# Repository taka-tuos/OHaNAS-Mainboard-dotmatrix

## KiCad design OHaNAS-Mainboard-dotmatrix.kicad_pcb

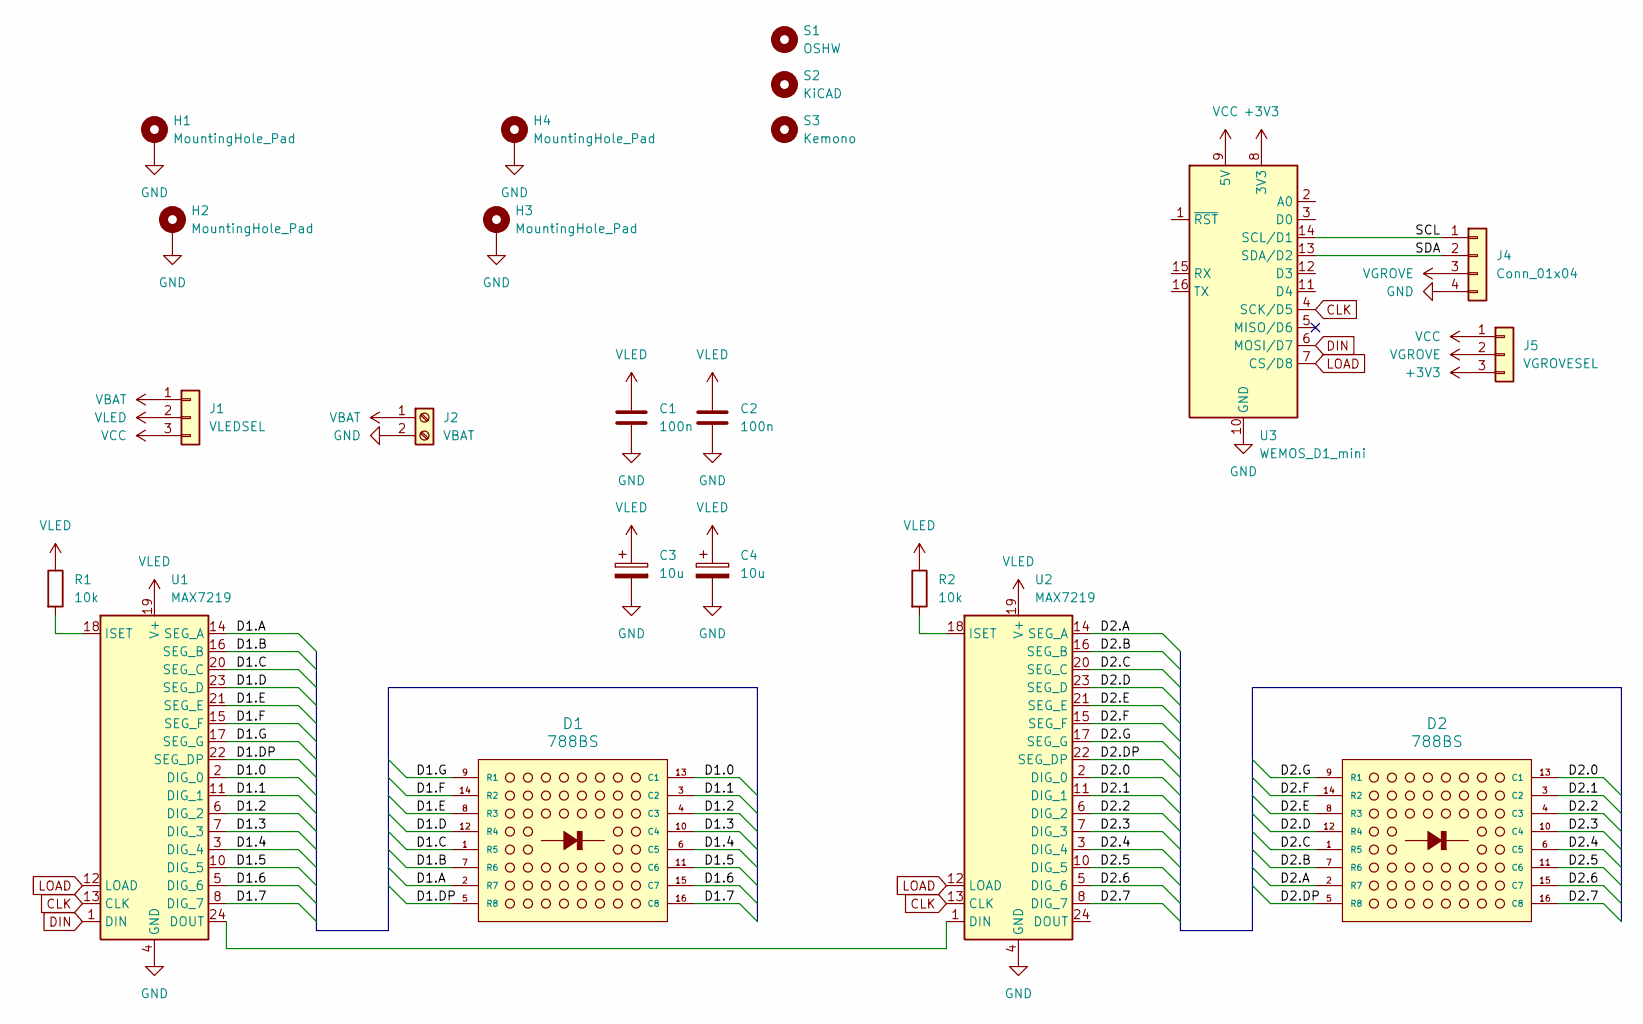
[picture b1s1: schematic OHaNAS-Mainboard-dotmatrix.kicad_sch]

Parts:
C1, C2: 100n; C_0805_2012Metric_Pad1.18x1.45mm_HandSolder
C3, C4: 10u; CP_Radial_D4.0mm_P1.50mm
D1, D2: 788BS; LED_8x8_1.9MM_20x20MM
H1, H2, H3, H4: MountingHole_Pad; MountingHole_2.7mm_M2.5_DIN965_Pad
J1: VLEDSEL; PinHeader_1x03_P2.54mm_Vertical
J2: VBAT; TerminalBlock_MaiXu_MX126-5.0-02P_1x02_P5.00mm
J4: Conn_01x04; NS-Tech_Grove_1x04_P2mm_Vertical
J5: VGROVESEL; PinHeader_1x03_P2.54mm_Vertical
R1, R2: 10k; R_0805_2012Metric_Pad1.20x1.40mm_HandSolder
S1: OSHW; OSHW-Logo_5.7x6mm_SilkScreen
S2: KiCAD; KiCad-Logo2_5mm_SilkScreen
S3: Kemono; Kemono_Symbol
U1, U2: MAX7219; SOIC-24W_7.5x15.4mm_P1.27mm
U3: WEMOS_D1_mini; WEMOS_D1_mini_light

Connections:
+3V3: J5.3, U3.8 (3V3)
/D1.0: D1.13 (C1), U1.2 (DIG_0)
/D1.1: D1.3 (C2), U1.11 (DIG_1)
/D1.2: D1.4 (C3), U1.6 (DIG_2)
/D1.3: D1.10 (C4), U1.7 (DIG_3)
/D1.4: D1.6 (C5), U1.3 (DIG_4)
/D1.5: D1.11 (C6), U1.10 (DIG_5)
/D1.6: D1.15 (C7), U1.5 (DIG_6)
/D1.7: D1.16 (C8), U1.8 (DIG_7)
/D1.A: D1.2 (R7), U1.14 (SEG_A)
/D1.B: D1.7 (R6), U1.16 (SEG_B)
/D1.C: D1.1 (R5), U1.20 (SEG_C)
/D1.D: D1.12 (R4), U1.23 (SEG_D)
/D1.DP: D1.5 (R8), U1.22 (SEG_DP)
/D1.E: D1.8 (R3), U1.21 (SEG_E)
/D1.F: D1.14 (R2), U1.15 (SEG_F)
/D1.G: D1.9 (R1), U1.17 (SEG_G)
/D2.0: D2.13 (C1), U2.2 (DIG_0)
/D2.1: D2.3 (C2), U2.11 (DIG_1)
/D2.2: D2.4 (C3), U2.6 (DIG_2)
/D2.3: D2.10 (C4), U2.7 (DIG_3)
/D2.4: D2.6 (C5), U2.3 (DIG_4)
/D2.5: D2.11 (C6), U2.10 (DIG_5)
/D2.6: D2.15 (C7), U2.5 (DIG_6)
/D2.7: D2.16 (C8), U2.8 (DIG_7)
/D2.A: D2.2 (R7), U2.14 (SEG_A)
/D2.B: D2.7 (R6), U2.16 (SEG_B)
/D2.C: D2.1 (R5), U2.20 (SEG_C)
/D2.D: D2.12 (R4), U2.23 (SEG_D)
/D2.DP: D2.5 (R8), U2.22 (SEG_DP)
/D2.E: D2.8 (R3), U2.21 (SEG_E)
/D2.F: D2.14 (R2), U2.15 (SEG_F)
/D2.G: D2.9 (R1), U2.17 (SEG_G)
/SCL: J4.1, U3.14 (SCL/D1)
/SDA: J4.2, U3.13 (SDA/D2)
CLK: U1.13 (CLK), U2.13 (CLK), U3.4 (SCK/D5)
DIN: U1.1 (DIN), U3.6 (MOSI/D7)
GND: C1.2, C2.2, C3.2, C4.2, H1.1, H2.1, H3.1, H4.1, J2.2, J4.4, U1.4 (GND), U1.9 (GND), U2.4 (GND), U2.9 (GND), U3.10 (GND)
LOAD: U1.12 (LOAD), U2.12 (LOAD), U3.7 (CS/D8)
unnamed: U1.24 (DOUT), U2.1 (DIN)
unnamed: R1.2, U1.18 (ISET)
unnamed: R2.2, U2.18 (ISET)
VBAT: J1.1, J2.1
VCC: J1.3, J5.1, U3.9 (5V)
VGROVE: J4.3, J5.2
VLED: C1.1, C2.1, C3.1, C4.1, J1.2, R1.1, R2.1, U1.19 (V+), U2.19 (V+)

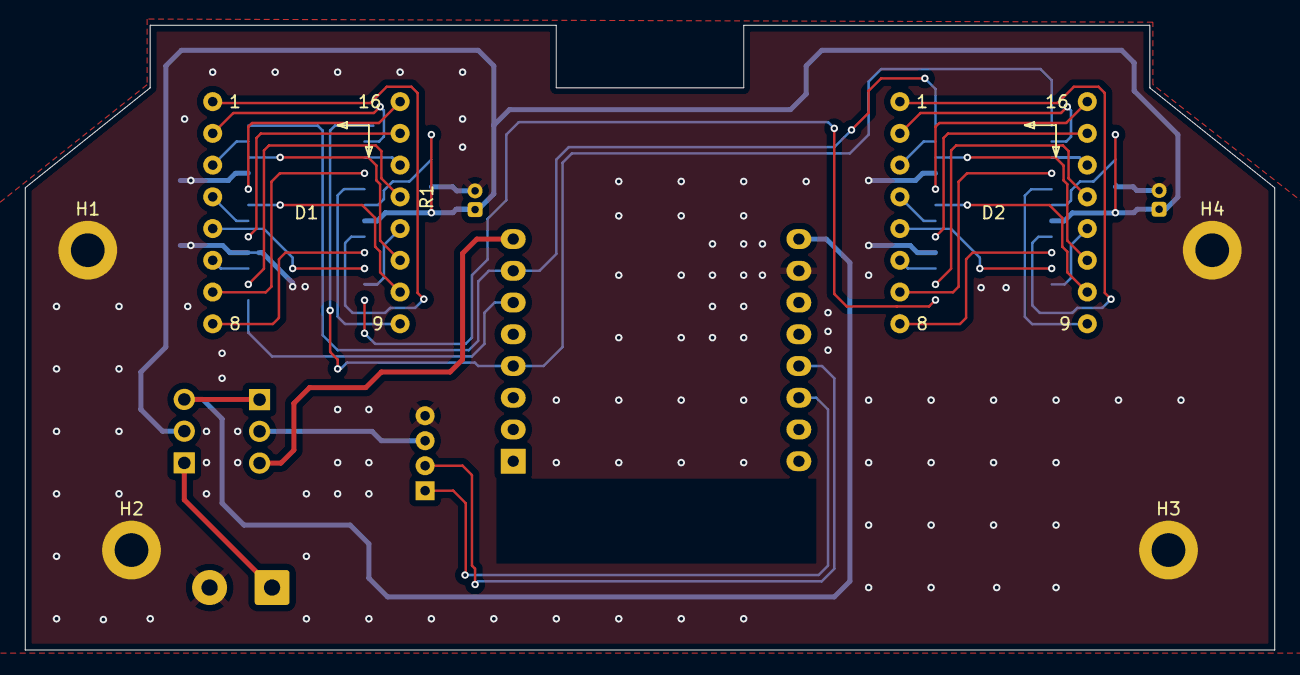
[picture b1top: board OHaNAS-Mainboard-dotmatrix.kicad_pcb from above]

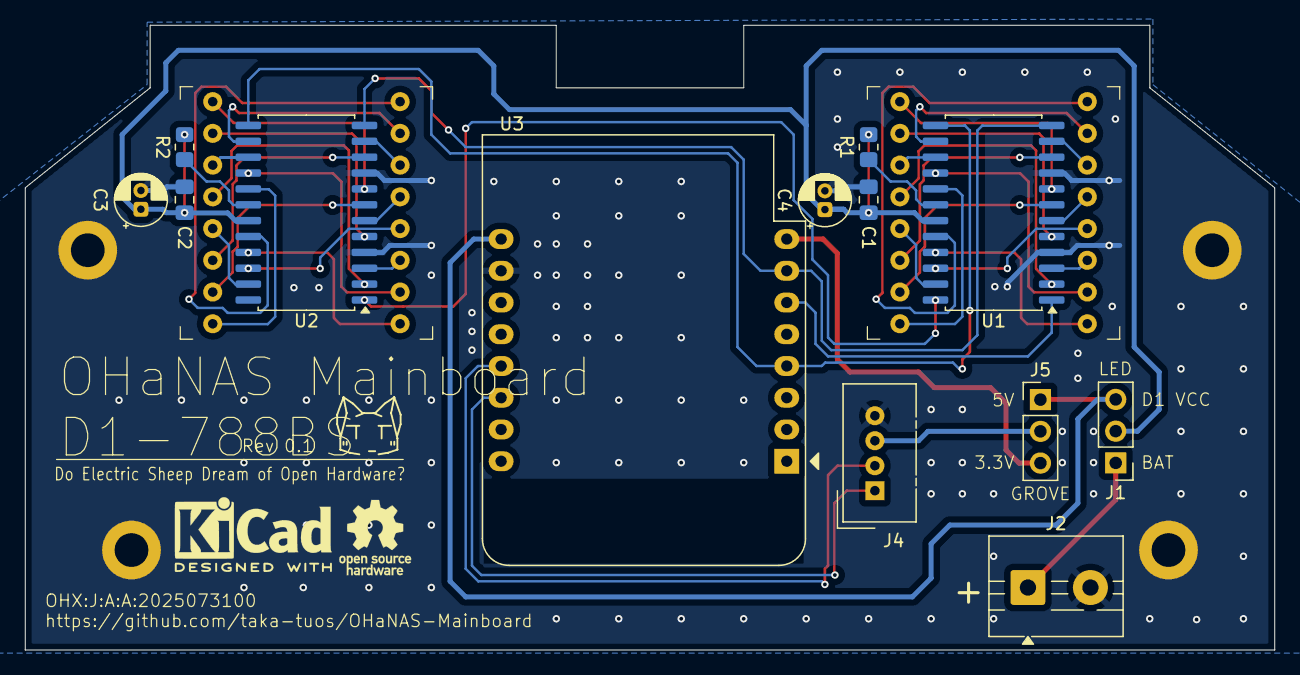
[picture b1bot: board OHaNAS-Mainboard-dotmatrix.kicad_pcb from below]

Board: 2 copper layers, 100.0 x 50.0 mm, 22 parts (16 on the bottom side), 46 nets.

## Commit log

2025-11-01 浄化
    GPLv3はすべてを解決します
